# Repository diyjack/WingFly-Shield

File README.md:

# WingFly-Shield
The WingFly-Shield extends all pins of the Arduino out to screw terminals (2.54mm pitch).

## Shop
* [WingFly-Shield](http://www.watterott.com/en/Arduino-WingFly-Shield)

## Hardware
* [Schematics + Layout](https://github.com/watterott/WingFly-Shield/tree/master/pcb)

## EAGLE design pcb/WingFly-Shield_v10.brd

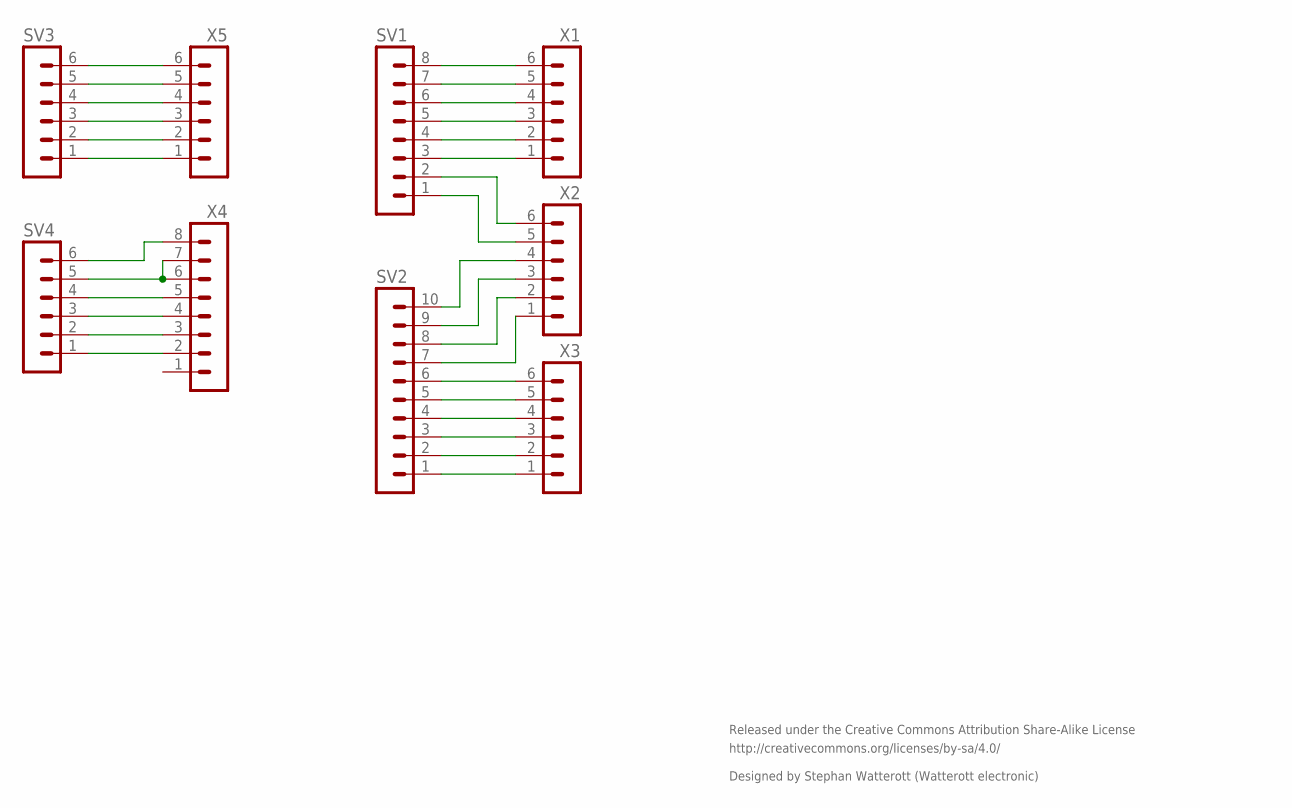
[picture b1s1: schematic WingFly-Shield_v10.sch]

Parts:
SV1: MA08-1
SV2: MA10-1
SV3, SV4: MA06-1
X1, X2, X3, X5: MA06-1
X4: MA08-1

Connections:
3V3: SV4.3, X4.4
5V: SV4.4, X4.5
A0: SV3.1, X5.1
A1: SV3.2, X5.2
A2: SV3.3, X5.3
A3: SV3.4, X5.4
A4: SV3.5, X5.5
A5: SV3.6, X5.6
AREF: SV2.3, X3.3
D0: SV1.8, X1.6
D1: SV1.7, X1.5
D2: SV1.6, X1.4
D3: SV1.5, X1.3
D4: SV1.4, X1.2
D5: SV1.3, X1.1
D6: SV1.2, X2.6
D7: SV1.1, X2.5
D8: SV2.10, X2.4
D9: SV2.9, X2.3
D10: SV2.8, X2.2
D11: SV2.7, X2.1
D12: SV2.6, X3.6
D13: SV2.5, X3.5
GND: SV4.5, X4.6, X4.7
GND2: SV2.4, X3.4
IOREF: SV4.1, X4.2
RST: SV4.2, X4.3
SCL: SV2.1, X3.1
SDA: SV2.2, X3.2
VIN: SV4.6, X4.8

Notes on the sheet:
Released under the Creative Commons Attribution Share-Alike License
http://creativecommons.org/licenses/by-sa/4.0/
Designed by Stephan Watterott (Watterott electronic)

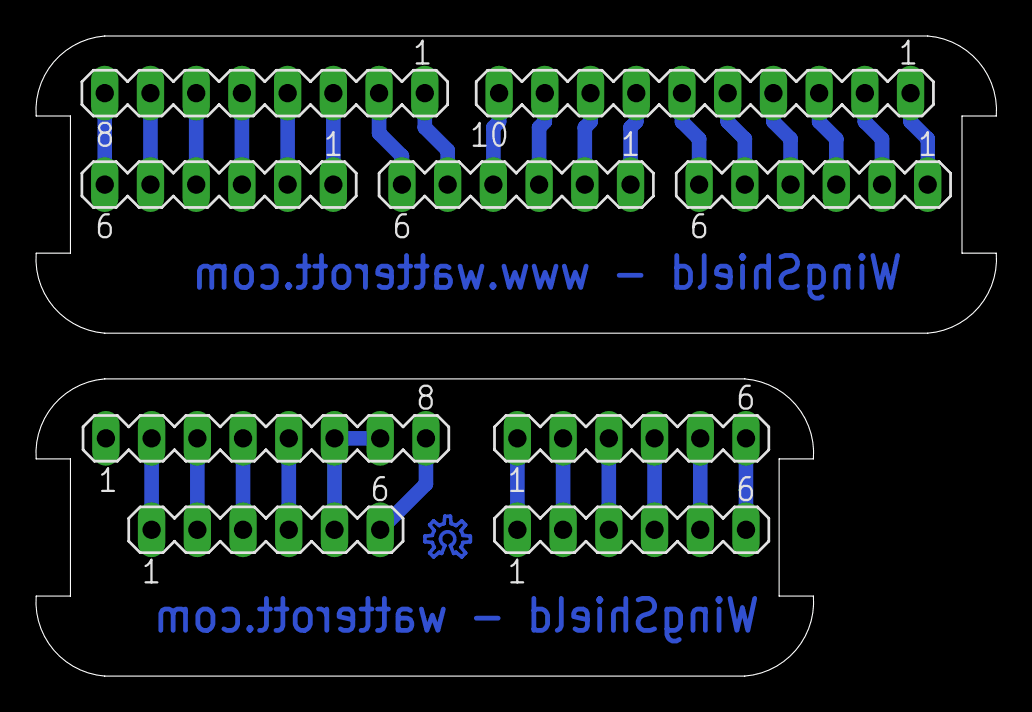
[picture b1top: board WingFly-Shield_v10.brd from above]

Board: 2 copper layers, 53.4 x 35.6 mm, 9 parts (0 on the bottom side), 30 nets.

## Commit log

2013-04-30 added layout
2014-03-10 updated license infos
2014-08-21 updated layout and schematics
2014-11-06 cleaned up schematics and layout
2015-01-11 moved image
2015-01-11 typo fix
